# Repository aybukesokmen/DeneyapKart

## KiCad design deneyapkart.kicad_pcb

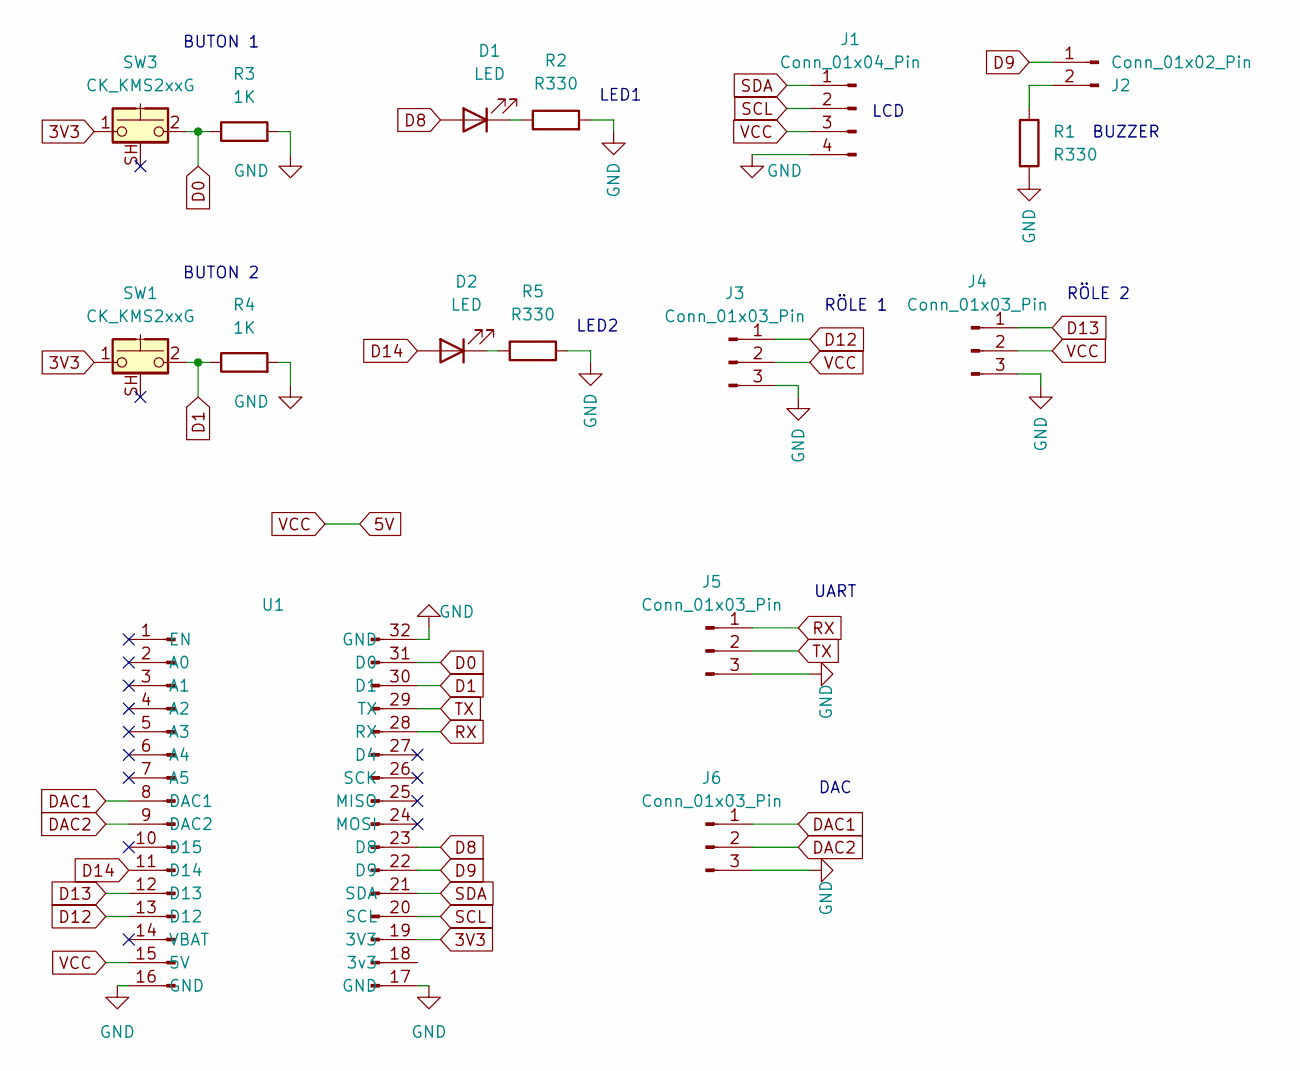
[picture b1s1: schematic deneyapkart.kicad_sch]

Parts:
D1, D2: LED; LED_D3.0mm
J1: Conn_01x04_Pin; TerminalBlock_4Ucon_1x04_P3.50mm_Horizontal
J2: Conn_01x02_Pin; TerminalBlock_4Ucon_1x02_P3.50mm_Horizontal
J3, J4, J5, J6: Conn_01x03_Pin; TerminalBlock_4Ucon_1x03_P3.50mm_Horizontal
R1, R2, R5: R330; R_Axial_DIN0204_L3.6mm_D1.6mm_P5.08mm_Horizontal
R3, R4: 1K; R_Axial_DIN0204_L3.6mm_D1.6mm_P5.08mm_Horizontal
SW1, SW3: CK_KMS2xxG; SW_PUSH_6mm_H4.3mm
U1: deneyapkart

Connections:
3V3: SW1.1, SW3.1, U1.18 (3v3), U1.19 (3V3)
5V: J1.3, J3.2, J4.2, U1.15 (5V)
D0: R3.1, SW3.2, U1.31 (D0)
D1: R4.1, SW1.2, U1.30 (D1)
D8: D1.2 (A), U1.23 (D8)
D9: J2.1, U1.22 (D9)
D12: J3.1, U1.13 (D12)
D13: J4.1, U1.12 (D13)
D14: D2.2 (A), U1.11 (D14)
DAC1: J6.1, U1.8 (DAC1)
DAC2: J6.2, U1.9 (DAC2)
GND: J1.4, J3.3, J4.3, J5.3, J6.3, R1.2, R2.2, R3.2, R4.2, R5.2, U1.16 (GND), U1.17 (GND), U1.32 (GND)
unnamed: D1.1 (K), R2.1
unnamed: D2.1 (K), R5.1
unnamed: J2.2, R1.1
RX: J5.1, U1.28 (RX)
SCL: J1.2, U1.20 (SCL)
SDA: J1.1, U1.21 (SDA)
TX: J5.2, U1.29 (TX)

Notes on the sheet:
LED1
UART
LCD
BUTON 2
RÖLE 2
RÖLE 1
DAC
BUZZER
LED2
BUTON 1

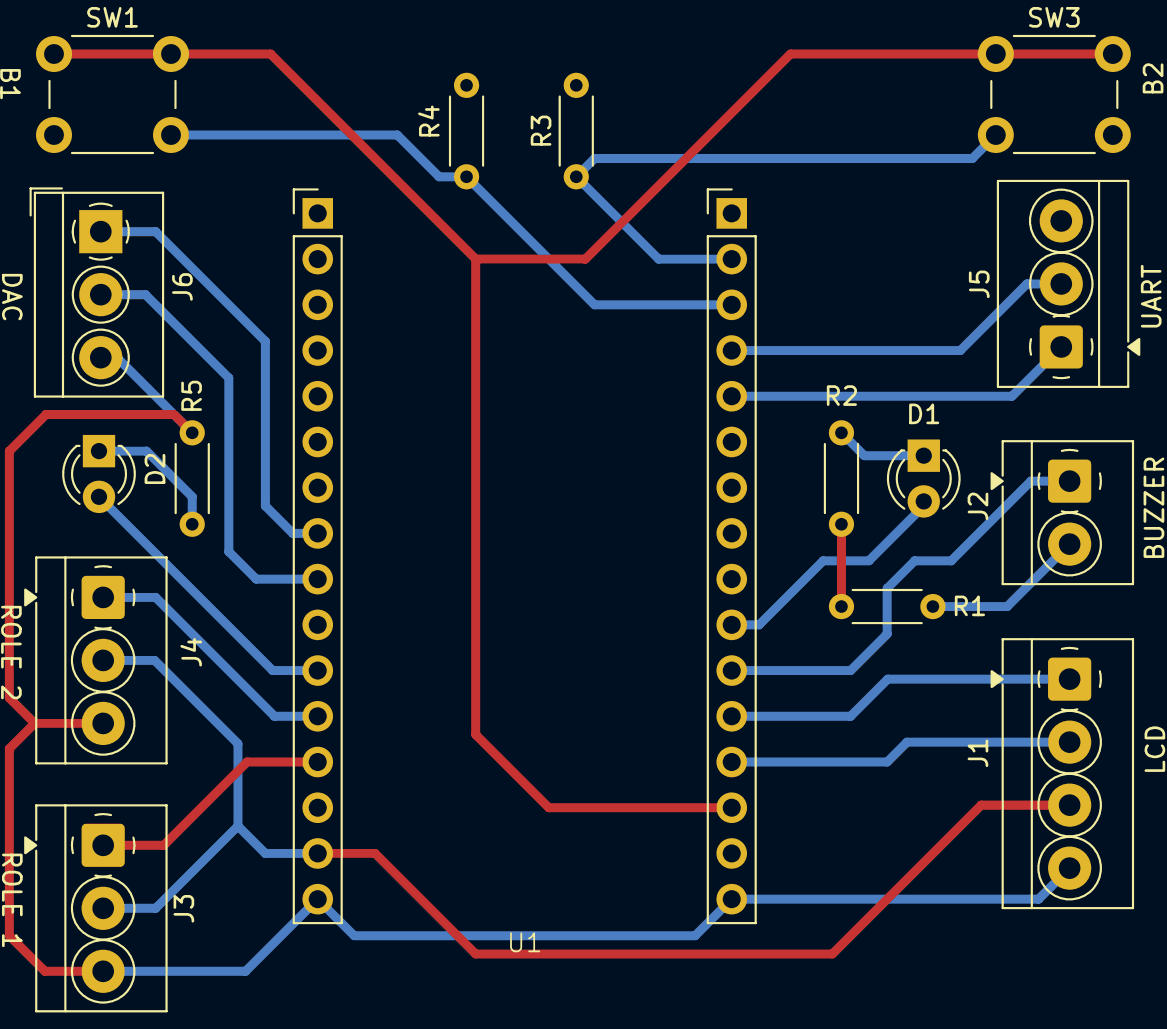
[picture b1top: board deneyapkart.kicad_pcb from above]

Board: 2 copper layers, 16 parts (0 on the bottom side), 19 nets.

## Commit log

2025-05-11 kutuphaneler olusuturuldu
2025-05-12 footprintleri secildi
2025-05-12 footprintler düzenlendi . bomlist olusturuldu, ground plane yollar cizildi
2025-05-12 resim eklendi
